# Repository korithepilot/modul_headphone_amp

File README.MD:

# Current Version:
## Top view:

## Bottom view:

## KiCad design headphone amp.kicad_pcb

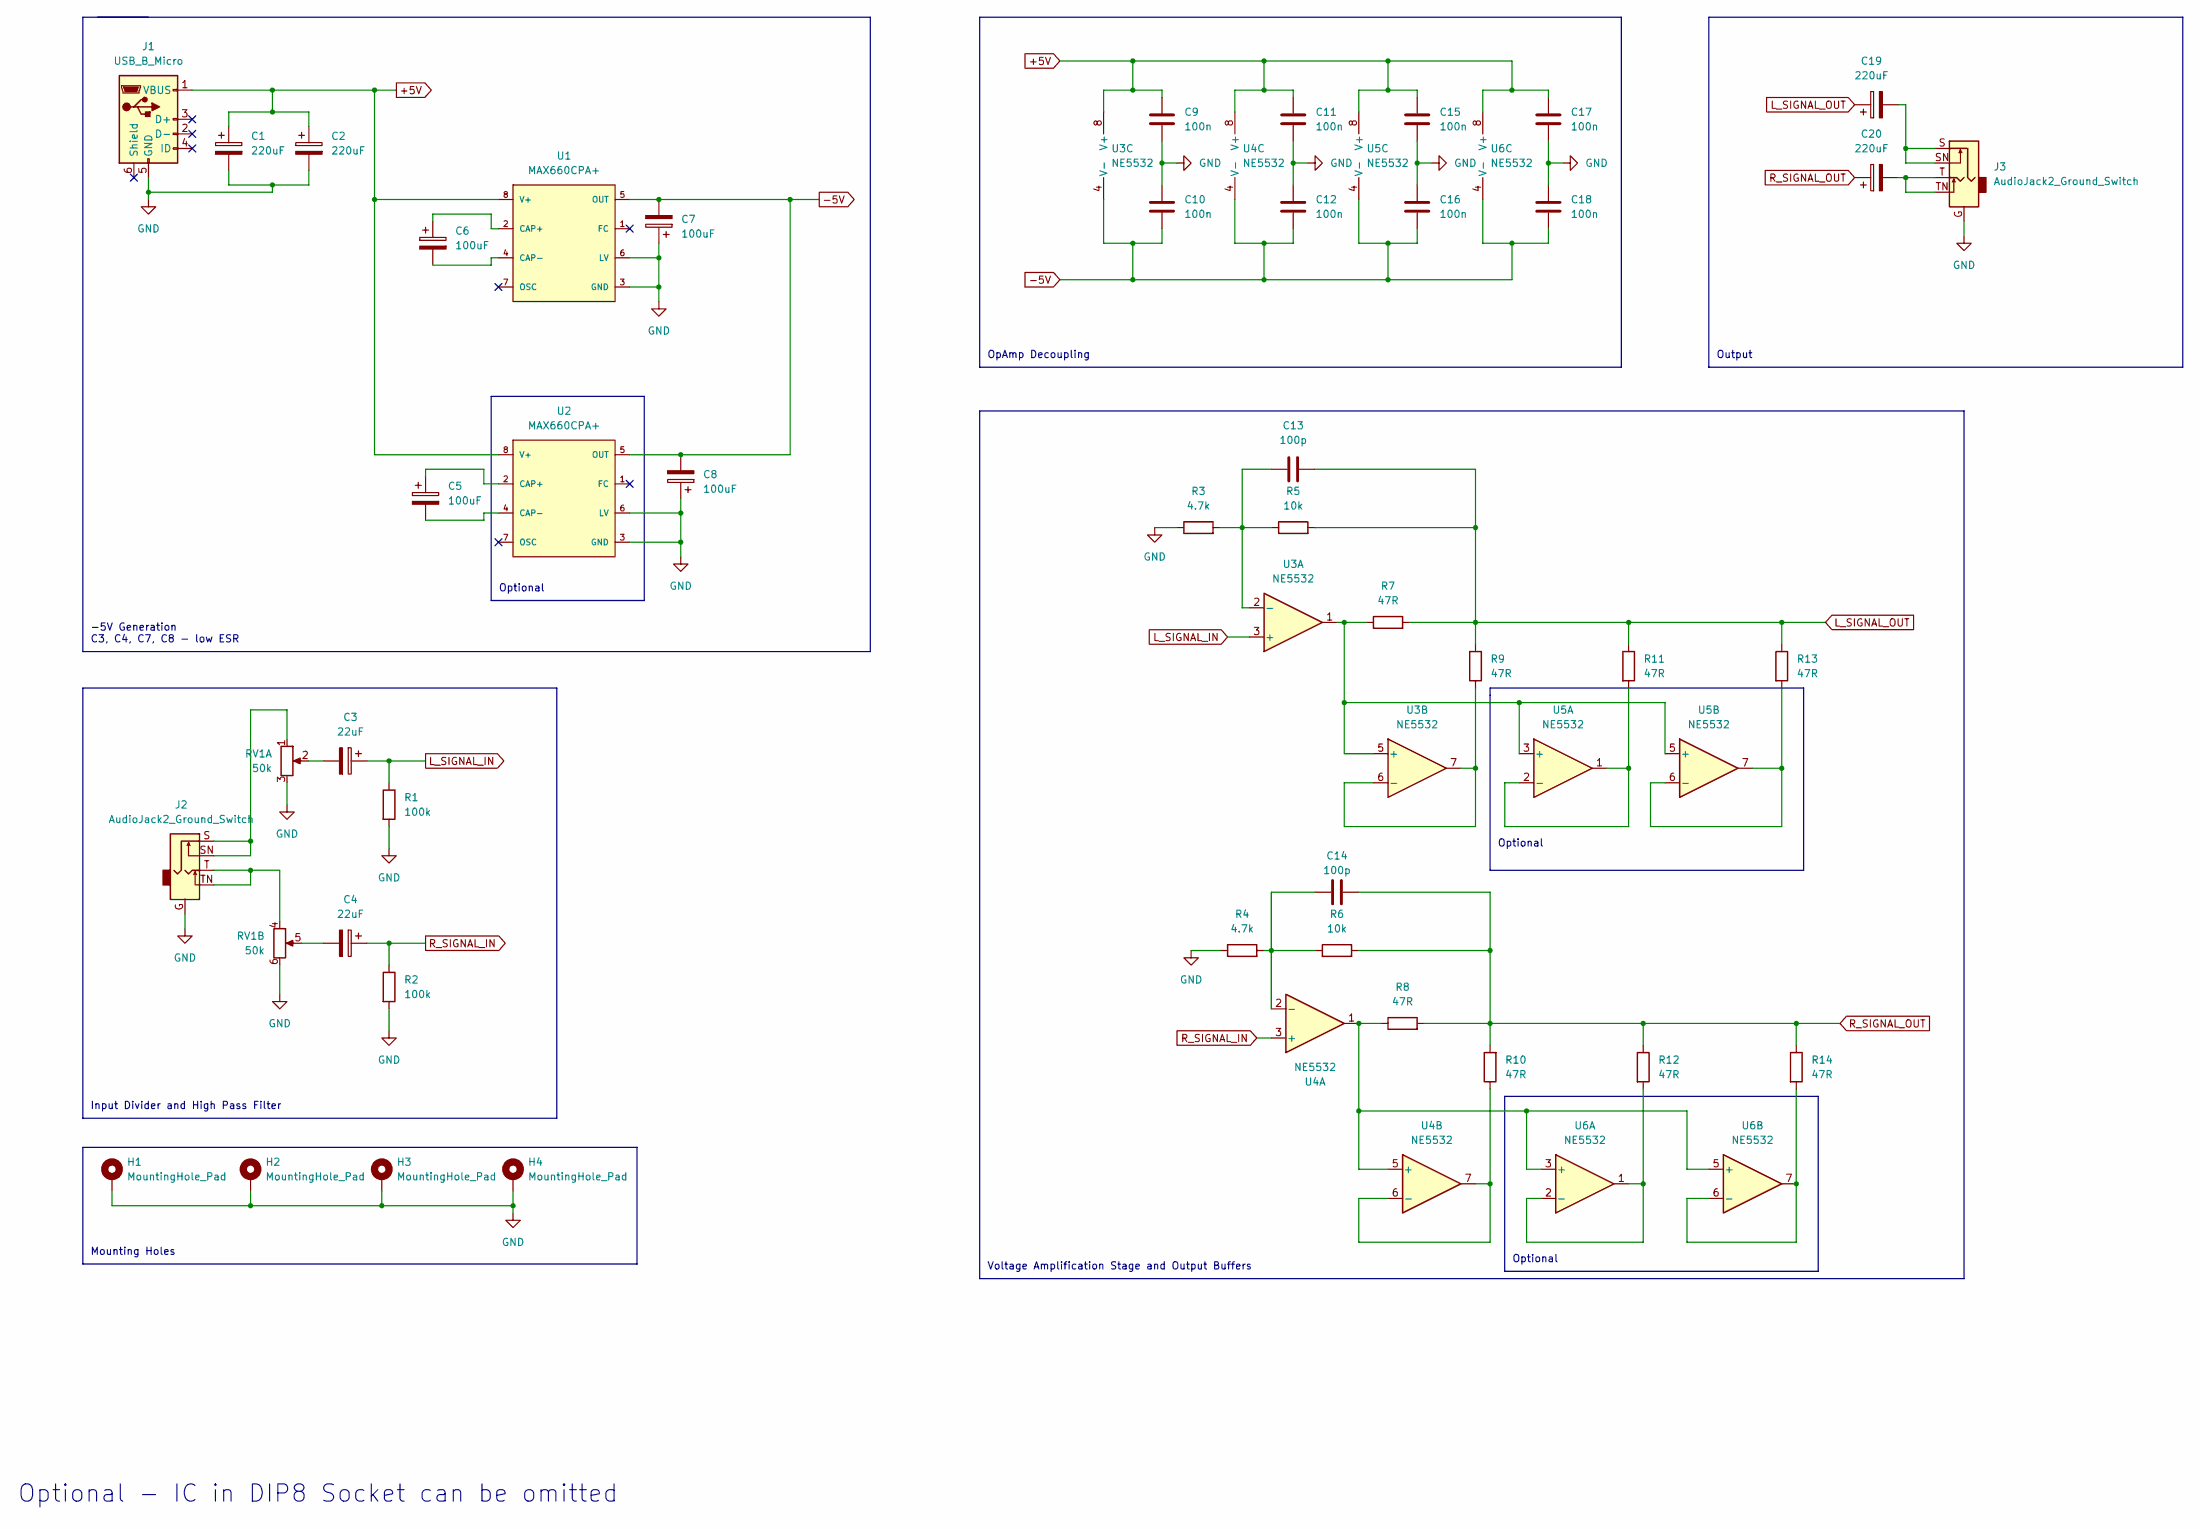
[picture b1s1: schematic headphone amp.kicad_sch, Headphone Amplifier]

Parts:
C1, C2, C19, C20: 220uF; CP_Radial_D8.0mm_P3.50mm
C3, C4: 22uF; CP_Radial_D6.3mm_P2.50mm
C5, C6, C7, C8: 100uF; CP_Radial_D6.3mm_P2.50mm
C9, C10, C11, C12, C15, C16, C17, C18: 100n; C_Rect_L7.2mm_W2.5mm_P5.00mm_FKS2_FKP2_MKS2_MKP2
C13, C14: 100p; C_0805_2012Metric_Pad1.18x1.45mm_HandSolder
H1, H2, H3, H4: MountingHole_Pad; MountingHole_3.2mm_M3_Pad
J1: USB_B_Micro; USB_Micro-B_Amphenol_10118194_Horizontal
J2, J3: AudioJack2_Ground_Switch; Jack_3.5mm_CUI_SJ1-3525N_Horizontal
R1, R2: 100k; R_0805_2012Metric_Pad1.20x1.40mm_HandSolder
R3, R4: 4.7k; R_0805_2012Metric_Pad1.20x1.40mm_HandSolder
R5, R6: 10k; R_0805_2012Metric_Pad1.20x1.40mm_HandSolder
R7, R8, R9, R10, R11, R12, R13, R14: 47R; R_0805_2012Metric_Pad1.20x1.40mm_HandSolder
RV1: 50k; Potentiometer_Alps_RK163_Dual_Horizontal
U1, U2: MAX660CPA+; DIP-8_W7.62mm_Socket_LongPads; negative voltage availa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 true; output voltage -5.5/+11V; mouser part number 700-MAX660CPA; digikey description IC REG CHARG PUMP INV 100MA 8DIP
U3, U4, U5, U6: NE5532; DIP-8_W7.62mm_Socket_LongPads

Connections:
+5V: C1.1, C2.1, C9.1, C11.1, C15.1, C17.1, J1.1 (VBUS), U1.8 (V+), U2.8 (V+), U3.8 (V+), U4.8 (V+), U5.8 (V+), U6.8 (V+)
-5V: C7.2, C8.2, C10.2, C12.2, C16.2, C18.2, U1.5 (OUT), U2.5 (OUT), U3.4 (V-), U4.4 (V-), U5.4 (V-), U6.4 (V-)
L_SIGNAL_IN: C3.1, R1.1, U3.3 (+)
L_SIGNAL_OUT: C13.1, C19.1, R5.2, R7.2, R9.2, R11.1, R13.1
unnamed: C3.2, RV1.2
unnamed: C4.2, RV1.5
unnamed: C5.1, U2.2 (CAP+)
unnamed: C5.2, U2.4 (CAP-)
unnamed: C6.1, U1.2 (CAP+)
unnamed: C6.2, U1.4 (CAP-)
unnamed: C13.2, R3.2, R5.1, U3.2 (-)
unnamed: C14.2, R4.2, R6.1, U4.2 (-)
unnamed: C19.2, J3.S, J3.SN
unnamed: C20.2, J3.T, J3.TN
unnamed: J2.S, J2.SN, RV1.1
unnamed: J2.T, J2.TN, RV1.4
unnamed: R7.1, U3.1, U3.5 (+), U5.3 (+), U5.5 (+)
unnamed: R8.1, U4.1, U4.5 (+), U6.3 (+), U6.5 (+)
unnamed: R9.1, U3.6 (-), U3.7
unnamed: R10.1, U4.6 (-), U4.7
unnamed: R11.2, U5.1, U5.2 (-)
unnamed: R12.2, U6.1, U6.2 (-)
unnamed: R13.2, U5.6 (-), U5.7
unnamed: R14.2, U6.6 (-), U6.7
R_SIGNAL_IN: C4.1, R2.1, U4.3 (+)
R_SIGNAL_OUT: C14.1, C20.1, R6.2, R8.2, R10.2, R12.1, R14.1

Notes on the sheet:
Mounting Holes
Input Divider and High Pass Filter
OpAmp Decoupling
-5V Generation C3, C4, C7, C8 - low ESR
Output
Optional
Voltage Amplification Stage and Output Buffers
Optional - IC in DIP8 Socket can be omitted

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
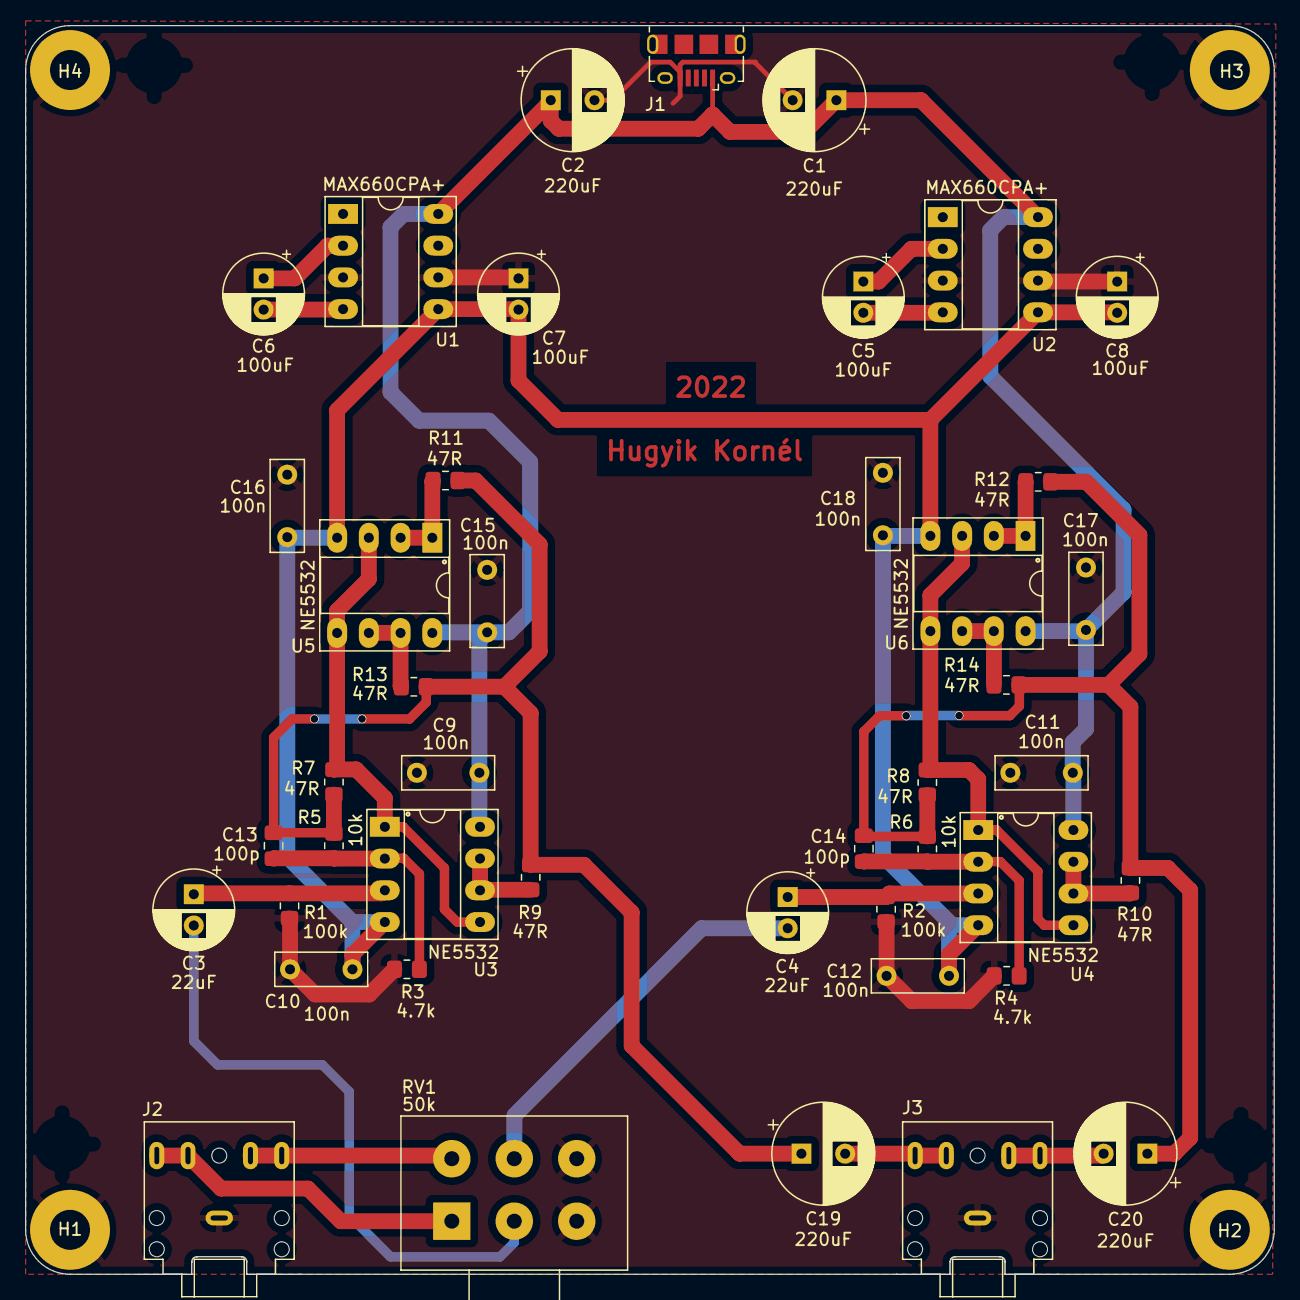
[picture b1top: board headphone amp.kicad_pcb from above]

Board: 2 copper layers, 99.9 x 99.9 mm, 48 parts (0 on the bottom side), 27 nets.

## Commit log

2022-10-30 Vasárnap esti layout terv
2022-10-30 Edge Cuts fix
2022-10-30 Pictures
2022-10-30 readme
2022-11-01 Rounded Corners, Signature and Updated Fab files
2022-11-01 Images for new version
2022-11-01 New Version Images
2022-11-03 Fixed one wire and added silly graphics
